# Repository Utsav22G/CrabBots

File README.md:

# CrabBots
### Small robots that use colored light to interact with other robots and the environment to perform complex interactions. 

## Overview
To learn more about our project, visit our [website!](http://poe.olin.edu/2018/crabworks/)

This github serves a storage capsule for our CAD files, PCB designs, and code used in our project. 

## PCB (Robot)
Our PCB is based off the Arduino Uno and includes some additional features:
* An analog mux for an increased number of anlog input pins
* A dual h-bridge motor driver to power our motors
* A 3-axis accelerometer for tap/bump detection
* Support for an RGB strip. We used NeoPixels

Because our PCB follows the same avr architecture as the Arduino Uno (and uses the same Atmega328P-PB), any Arduino code can be
uploaded through the Arduino IDE compiler to program our boards. However, our boards are lacking usb-serial convertera so an external
usb-serial converter is needed ([this is what we used](https://www.sparkfun.com/products/9825)).

You might notice that our assembled PCBs are populated with only a fraction of the parts that are included in our layout. This is 
due to a radical change in our photodiode sensing circuit after shipping the boards to be manufactured. Fortunately, our new circuit
uses less parts so it's still easy to assemble a working board. 

If you are up for an extra challenge, feel free to submit a pull request for a flashy, new board.

## PCB (Beacon)
What is the best accessory for our CrabBot? A fancy flashlight that can be programmed to display any color and controlled with a
tactile toggle button, of course! Our beacons are a useful tool for debugging and controlling our bots.

The schematic for the board stayed mostly the same. An input for **gnd** and **vcc** are needed for the board to function. We also recommend adding a power switch so the Attiny 85 doesn't drain your battery over time.

## Software
Our final bots rely on two code files: chaser, chased. When uploaded to our CrabBots, this code will make them chase each other. The code is written in Arduino and relys on multiple libraries including the Adafruit sensor library. The appropriate packages that need to be downloaded can be found [here](https://learn.adafruit.com/adafruit-lis3dh-triple-axis-accelerometer-breakout/arduino) and [here](https://learn.adafruit.com/adafruit-neopixel-uberguide/basic-connections). 

## Mechanical Design
The final iteration of CAD can be found here. We printed the components on a Prusa with PLA filament. While this design should not
be constrained by the type of plastic or printer used, we can't guarantee success with another setup. 

## Assembly
While we currently don't have a thorough instruction set layed out, we recommend looking at all our pictures. You probably don't need
or want instructions anyways!

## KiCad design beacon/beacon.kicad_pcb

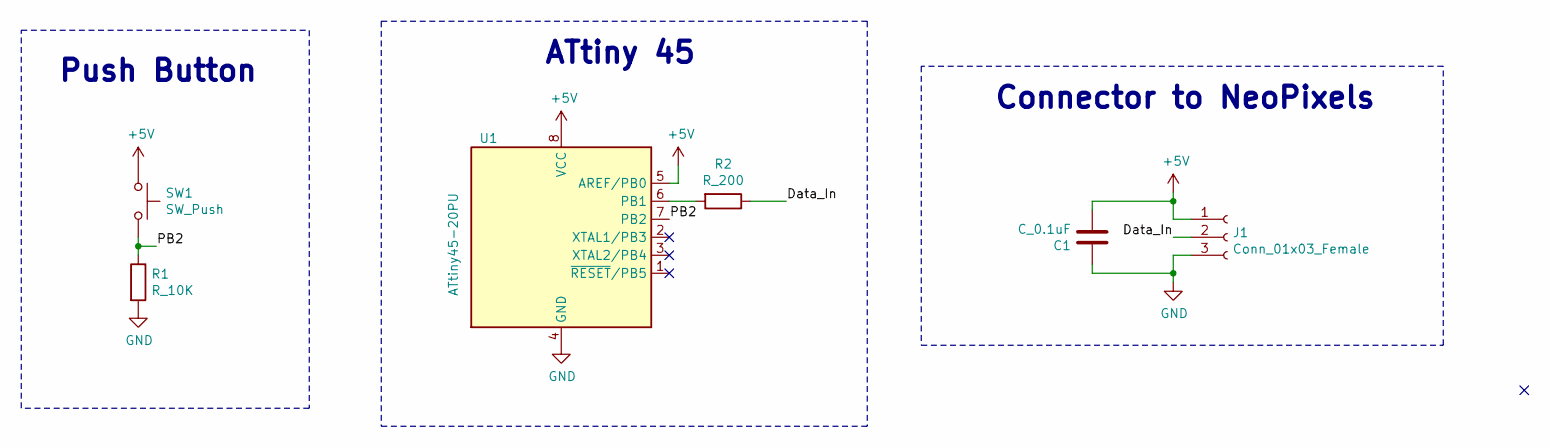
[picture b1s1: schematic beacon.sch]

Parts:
C1: C_0.1uF; C_0805_OEM; MPN 478-3352-1-ND
J1: Conn_01x03_Female; Connector
R1: R_10K; R_0805_OEM; MPN CRS0805-FX-1002ELFCT-ND
R2: R_200; R_0805_OEM; MPN RMCF0805JT200RCT-ND
SW1: SW_Push; push_button
U1: ATtiny45-20PU; DIP-8_W7.62mm_Socket

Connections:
+5V: C1.2, J1.1, SW1.1, U1.5 (AREF/PB0), U1.8 (VCC)
/Data_In: J1.2, R2.1
/PB2: R1.1, SW1.2, U1.7 (PB2)
GND: C1.1, J1.3, R1.2, U1.4 (GND)
unnamed: R2.2, U1.6 (PB1)

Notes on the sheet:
ATtiny 45
Connector to NeoPixels
Push Button

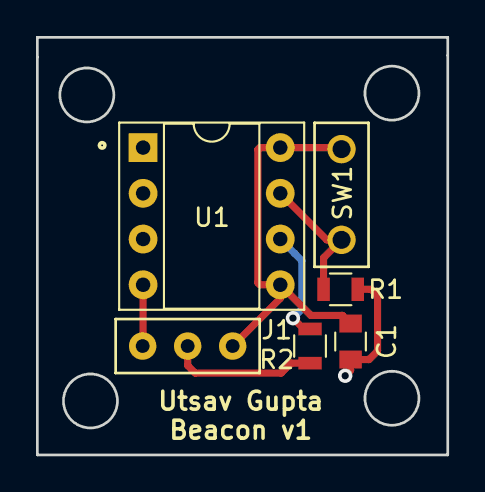
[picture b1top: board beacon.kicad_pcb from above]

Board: 2 copper layers, 22.8 x 23.2 mm, 6 parts (0 on the bottom side), 5 nets.

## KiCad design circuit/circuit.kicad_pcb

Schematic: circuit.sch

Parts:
C1, C7, C8, C9, C10: C_0.1uF; C_0805_OEM; MPN 478-3352-1-ND
C2, C3: C_30pF; C_0805_OEM; MPN 1276-1130-1-ND
C4: C_100pF; C_0805_OEM; MPN 399-1122-1-ND
C5: C_0.01uF; C_0805_OEM; MPN 478-3352-1-ND
C6: C_2.2uF; R_0805_OEM; MPN 311-1451-1-ND
D1, D2: LED_0805; LED_0805_OEM; MPN 475-1410-1-ND
F1: Fuse_1A; R_0805_OEM
J1: Conn_01x20_Female; Pin_Header_Straight_2x10
J2: Conn_02x03_Odd_Even; Pin_Header_Straight_2x03
P1: CONN_02X03; Pin_Header_Straight_2x03; MPN 609-3234-ND
R1, R2, R7, R9, R19, R21, R29, R30: R_10K; R_0805_OEM; MPN CRS0805-FX-1002ELFCT-ND
R3, R12, R13, R14, R15, R24, R25: R_200; R_0805_OEM; MPN RMCF0805JT200RCT-ND
R4, R5, R16, R17: R_1M; R_0805_OEM; MPN RMCF0805JT1M00CT-ND
R6, R8, R10, R11, R18, R20, R22, R23: R_100K; R_0805_OEM; MPN P100KCCT-ND
R26: R_47K; R_0805_OEM; MPN RNCP0805FTD1K00CT-ND
R27: R_10k; R_0805_OEM; MPN CRS0805-FX-1002ELFCT-ND
R28: R_100; R_0805_OEM; MPN RNCP0805FTD100RCT-ND
U1: LMC6484; SOIC-14_3.9x8.7mm_Pitch1.27mm
U2: LIS3DHTR
U3, U4: LM358DT; SO-8_5.3x6.2mm_Pitch1.27mm
U5: L78M05CDT-TR
U6: LM3480; SOT-23; MPN LM3480IM3-3.3CT-ND
U7, U8: SN74LV4052APWR; TSSOP-16_4.4x5mm_Pitch0.65mm
U9: DRV8834; DRV8834PWP
U10: ATmega328P-PU; ATMEGA_328PB_CONN
Y1: Crystal_SMD; Crystal_SMD_FA238; MPN 887-1125-1-ND

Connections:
/3.3V: C8.1, C10.1, R1.2, R2.2, R30.1, U2.1, U2.14, U6.1
/MISO: P1.1, U10.18 (PB4)
/MOSI: P1.4, U10.17 (PB3)
/RESET: P1.5, R27.2, U10.1 (~RESET~/PC6)
/SCK: P1.3, U10.19 (PB5)
/SCL: R2.1, U2.4, U10.28 (PC5)
/SDA: R1.1, U2.6, U10.27 (PC4)
/battery+: C5.2, D1.2, F1.1, U5.1 (GND), U9.18, U9.19
/blue_1: J1.16, U7.1
/blue_2: J1.15, U7.5
/blue_3: J1.14, U7.2
/blue_4: J1.13, U7.4
/blue_5: J1.8, U8.1
/blue_6: J1.7, U8.5
/blue_7: J1.6, U8.2
/blue_8: J1.5, U8.4
/blue_inA: R17.2, U1.9 (-), U7.3
/blue_inB: R16.2, U1.13 (-), U8.3
/blue_outA: R25.1, U10.24 (PC1)
/blue_outB: R24.1, U10.26 (PC3)
/issues: U9.16, U10.12 (PD6)
/led_D1: R3.1, U10.13 (PD7)
/motorA+: J2.1, U9.4
/motorA-: J2.2, U9.6
/motorA_DIR: U9.13, U10.6 (PD4)
/motorA_PWM: U9.10, U10.15 (PB1)
/motorB+: J2.3, U9.9
/motorB-: J2.4, U9.7
/motorB_DIR: U9.12, U10.11 (PD5)
/motorB_PWM: U9.11, U10.16 (PB2)
/p_led: D2.2, U10.14 (PB0)
/red_1: J1.12, U7.12
/red_2: J1.11, U7.14
/red_3: J1.10, U7.15
/red_4: J1.9, U7.11
/red_5: J1.4, U8.12
/red_6: J1.3, U8.14
/red_7: J1.2, U8.15
/red_8: J1.1, U8.11
/red_inA: R4.2, U1.2 (-), U7.13
/red_inB: R5.2, U1.6 (-), U8.13
/red_outA: R12.1, U10.23 (PC0)
/red_outB: R13.1, U10.25 (PC2)
/select_0A: U7.10, U10.2 (PD0)
/select_0B: U8.10, U10.4 (PD2)
/select_1A: U7.9, U10.3 (PD1)
/select_1B: U8.9, U10.5 (PD3)
unnamed: C2.1, U10.9 (XTAL1/PB6), Y1.3
unnamed: C3.1, U10.10 (XTAL2/PB7), Y1.1
unnamed: C4.2, R28.1, U10.20 (AVCC)
unnamed: C5.1, U9.17
unnamed: D1.1, R14.2
unnamed: D2.1, R15.2
unnamed: F1.2, J2.5
unnamed: J1.19, R3.2
unnamed: R4.1, R7.2, U1.1
unnamed: R5.1, R9.2, U1.7
unnamed: R7.1, U3.3
unnamed: R9.1, U4.3
unnamed: R10.1, R12.2, U3.1
unnamed: R6.2, R10.2, U3.2
unnamed: R11.1, R13.2, U4.1
unnamed: R8.2, R11.2, U4.2
unnamed: R16.1, R19.2, U1.14
unnamed: R17.1, R21.2, U1.8
unnamed: R18.2, R22.2, U4.6
unnamed: R19.1, U4.5
unnamed: R20.2, R23.2, U3.6
unnamed: R21.1, U3.5
unnamed: R22.1, R24.2, U4.7
unnamed: R23.1, R25.2, U3.7
unnamed: R26.2, U9.1
unnamed: R29.1, U2.7
unnamed: R30.2, U2.8
VCC: C1.2, C6.1, C7.1, C9.1, J1.17, J1.18, P1.2, R26.1, R27.1, R28.2, U1.4 (V+), U3.8, U4.8, U5.2 (VO), U6.2, U7.16, U8.16, U9.20, U9.22, U9.23, U9.24, U10.7 (VCC)

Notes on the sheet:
RED DIODE CIRCUIT
BLUE DIODE CIRCUIT
ORIGINAL CIRCUIT
NEW CIRCUIT
CONNECTORS
MOTOR DRIVER
POWER REGULATORS
MAIN
PROGRAMMING
POWER
AUXILIARY HARDWARE
PINOUT
SUPPORTING IMAGES
LEDS
ACCELEROMETER

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
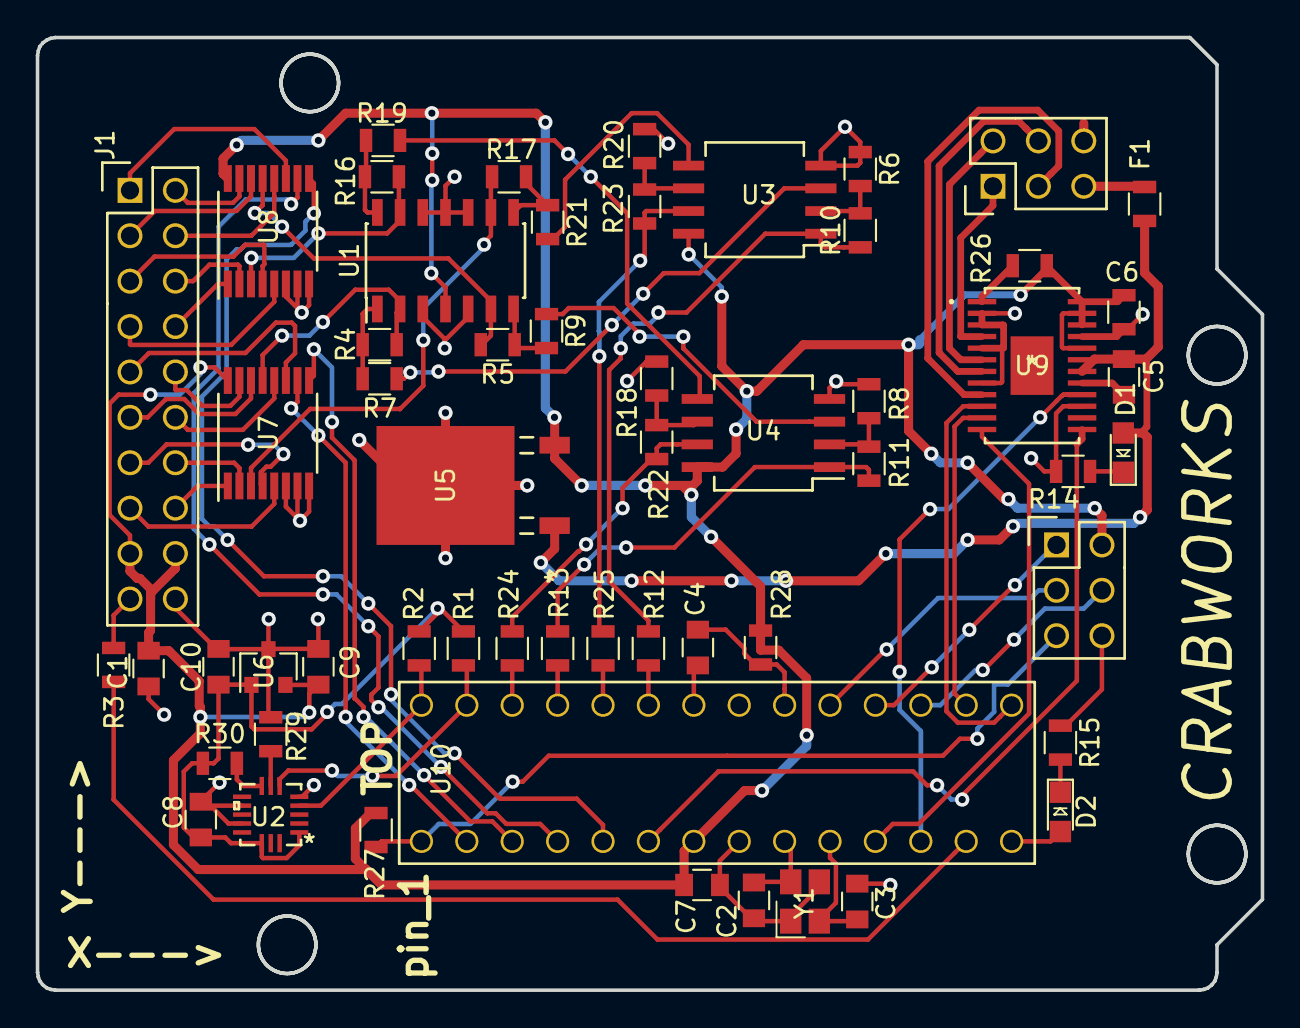
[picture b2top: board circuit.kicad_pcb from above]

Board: 2 copper layers, 68.5 x 53.3 mm, 57 parts (0 on the bottom side), 76 nets.

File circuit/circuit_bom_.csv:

Component,Description,Part,References,Value,Footprint,Quantity Per PCB,Datasheet,MPN,MFN,PurchasingLink,Package,Purchasing Link
1,"Capacitor, 0.1uF, 50V, 5%, 0805",C_0.1uF,C5,C_0.01uF,C_0805_OEM,1,http://datasheets.avx.com/X7RDielectric.pdf,478-3352-1-ND,DK,https://www.digikey.com/product-detail/en/samsung-electro-me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,,
2,"Capacitor, 0.1uF, 50V, 5%, 0805",C_0.1uF,C1 C7 C8 C9 C10,C_0.1uF,C_0805_OEM,5,http://datasheets.avx.com/X7RDielectric.pdf,478-3352-1-ND,DK Digi-Key,https://www.digikey.com/products/en?keywords=478-3352-1-ND,Value,
3,"Capacitor, 100pF, 50V, 5%, 0805",C_100pF,C4,C_100pF,C_0805_OEM,1,https://content.kemet.com/datasheets/KEM_C1003_C0G_SMD.pdf,399-1122-1-ND,Digi-Key,https://www.digikey.com/product-detail/en/kemet/C0805C101J5G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,Value,
4,"Capacitor, 2.2uF, 10V, 10%, 0603",C_2.2uF,C6,C_2.2uF,R_0805_OEM,1,http://www.yageo.com/documents/recent/UPY-GPHC_X5R_4V-to-50V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,311-1451-1-ND,DK,https://www.digikey.com/product-detail/en/taiyo-yuden/EMK212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,,
5,"Capacitor, 30pF, 50V, 5%, 0805",C_30pF,C2 C3,C_30pF,C_0805_OEM,2,https://media.digikey.com/pdf/Data%20Sheets/Samsung%20PDFs/C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,1276-1130-1-ND,DK,https://www.digikey.com/product-detail/en/samsung-electro-me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,,
6,"LED, Green, 2.2V, 20mA, 0805",LED_0805,D1 D2,LED_0805,LED_0805_OEM,2,http://www.osram-os.com/Graphics/XPic9/00078860_0.pdf,475-1410-1-ND,DK,https://www.digikey.com/products/en?keywords=475-1410-1-ND,,
7,Fuse,Fuse,F1,Fuse_1A,R_0805_OEM,1,https://industrial.panasonic.com/cdbs/www-data/pdf/AFA0000/A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,,,,,
8,"Generic connector, single row, 01x20, script generated (kicad-library-utils/schlib/autogen/connector/)",Conn_01x20_Female,J1,Conn_01x20_Female,Pin_Header_Straight_2x10,1,~,,,,,
9,"Generic connector, double row, 02x03, odd/even pin numbering scheme (row 1 odd numbers, row 2 even numbers), script generated (kicad-library-utils/schlib/autogen/connector/)",Conn_02x03_Odd_Even,J2,Conn_02x03_Odd_Even,Pin_Header_Straight_2x03,1,~,,,,,
10,,CONN_02X03-formula,P1,CONN_02X03,Pin_Header_Straight_2x03,1,http://portal.fciconnect.com/Comergent//fci/drawing/67996.pdf,609-3234-ND,Digi-Key,https://www.digikey.com/product-detail/en/amphenol-fci/67997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,Value,
11,,R_100,R28,R_100,R_0805_OEM,1,https://www.seielect.com/Catalog/SEI-rncp.pdf,RNCP0805FTD100RCT-ND,Digi-Key,https://www.digikey.com/products/en?keywords=RNCP0805FTD100RCT-ND,Value,
12,,R_100K,R6 R8 R10 R11 R18 R20 R22 R23,R_100K,R_0805_OEM,8,https://industrial.panasonic.com/cdbs/www-data/pdf/RDA0000/A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,P100KCCT-ND,DK,https://www.digikey.com/product-detail/en/panasonic-electron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,,
13,,R_10K,R1 R2 R7 R9 R19 R21 R29 R30,R_10K,R_0805_OEM,8,http://www.bourns.com/data/global/pdfs/CRS.pdf,CRS0805-FX-1002ELFCT-ND,DK,https://www.digikey.com/products/en?keywords=CRS0805-FX-1002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,,
14,,R_10k-formula,R27,R_10k,R_0805_OEM,1,http://www.bourns.com/data/global/pdfs/CRS.pdf,CRS0805-FX-1002ELFCT-ND,Digi-Key,https://www.digikey.com/products/en?keywords=CRS0805-FX-1002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,Value,
15,,R_1M,R4 R5 R16 R17,R_1M,R_0805_OEM,4,https://www.seielect.com/Catalog/SEI-rncp.pdf,RMCF0805JT1M00CT-ND,DK,https://www.digikey.com/product-detail/en/stackpole-electron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,,
16,,R_200,R3 R12 R13 R14 R15 R24 R25,R_200,R_0805_OEM,7,https://www.seielect.com/Catalog/SEI-RMCF_RMCP.pdf,RMCF0805JT200RCT-ND,DK,https://www.digikey.com/products/en?keywords=RMCF0805JT200RCT-ND,,
17,,R_1K,R26,R_47K,R_0805_OEM,1,https://www.seielect.com/Catalog/SEI-rncp.pdf,RNCP0805FTD1K00CT-ND,DK,https://www.digikey.com/products/en?keywords=RNCP0805FTD1K00CT-ND,,
18,,ATmega328P-PU-MCU_Microchip_ATmega,U10,ATmega328P-PU,ATMEGA_328PB_CONN,1,http://ww1.microchip.com/downloads/en/DeviceDoc/ATmega328_P%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,,,,,
19,,DRV8834-formula,U9,DRV8834,DRV8834PWP,1,www.ti.com/lit/ds/symlink/drv8834.pdf,,,,,https://www.digikey.com/product-detail/en/texas-instruments/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
20,"1A Low Dropout regulator, positive, 5.0V fixed output, SOT-223",AMS1117-5.0,U5,L78M05CDT-TR ,L78M05CDT-TR,1,www.st.com/content/ccc/resource/technical/document/datasheet/d7/5f/dc/5c/d5/b6/48/7c/CD00000447.pdf/files/CD00000447.pdf/jcr:content/translations/en.CD00000447.pdf,,,,,
21,,LIS3DHTR-formula,U2,LIS3DHTR,LIS3DHTR,1,,,,,,
22,"Linear regulator, 30V max input, 3.3V output, 100mA",LM3480,U6,LM3480,SOT-23,1,http://www.ti.com/lit/ds/symlink/lm3480.pdf,LM3480IM3-3.3CT-ND,DK,https://www.digikey.com/product-detail/en/texas-instruments/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,,
23,,LM358DT-formula,U3 U4,LM358DT,SO-8_5.3x6.2mm_Pitch1.27mm,2,www.st.com/content/ccc/resource/technical/document/datasheet/61/46/87/01/98/ed/44/c5/CD00000464.pdf/files/CD00000464.pdf/jcr:content/translations/en.CD00000464.pdf,,,https://www.digikey.com/product-detail/en/stmicroelectronics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,,
24,"Quad CMOS Rail-to-Rail Input and Output Operational Amplifier, DIP-14/SOIC-14",LMC6484,U1,LMC6484,SOIC-14_3.9x8.7mm_Pitch1.27mm,1,http://www.ti.com/lit/ds/symlink/lmc6484.pdf,,,,,
25,,SN74LV4052APWR-formula,U7 U8,SN74LV4052APWR,TSSOP-16_4.4x5mm_Pitch0.65mm,2,www.ti.com/lit/ds/symlink/sn74lv4052a.pdf,,,,,https://www.digikey.com/product-detail/en/texas-instruments/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
26,CRYSTAL 16.0000MHZ 18PF SMD,Crystal_SMD,Y1,Crystal_SMD,Crystal_SMD_FA238,1,http://www.txccorp.com/download/products/quartz_crystals/201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,887-1125-1-ND,DK,https://www.digikey.com/product-detail/en/txc-corporation/7M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,,
,,,,,,,,,,,,
,,,,,,,,,,,,
,,,,,,,,,,,,
,,,,,,,,,,,,
,,,,,,,,,,,,
Component Groups:,26,,,,,,,,,,,
Component Count:,57,,,,,,,,,,,
Fitted Components:,57,,,,,,,,,,,
Number of PCBs:,1,,,,,,,,,,,
Total components:,57,,,,,,,,,,,
Schematic Version:,,,,,,,,,,,,
Schematic Date:,,,,,,,,,,,,
BoM Date:,Wed 21 Nov 2018 11:47:25 PM EST,,,,,,,,,,,
Schematic Source:,/home/utsav22g/Olin Stuff/CrabBots/circuit/circuit.sch,,,,,,,,,,,
KiCad Version:,Eeschema 5.0.1-33cea8e~68~ubuntu18.04.1,,,,,,,,,,,

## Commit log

2018-10-17 Luminosity detector
2018-10-21 added new code for reading sensor values that could have changing frequencies
2018-10-21 added a schematic for our circuit
2018-10-28 added color sense code
2018-10-31 NeoPixels working code
2018-10-31 made progress on schematic
2018-11-01 Controlling NeoPixels with ATtiny45
2018-11-04 more progess git add -A!
2018-11-04 finished schematic for main board
2018-11-05 started on layout. *make crab noise*
2018-11-06 finished board
2018-11-06 Adding beacon schematic
2018-11-06 generated gerber files
2018-11-06 Adding gerber files
2018-11-07 added pictures of the pcb
2018-11-13 added accel pics
2018-11-25 added pics of layout for pcb
2018-11-25 added arduino code
2018-11-27 added more pics
2018-11-29 added code for driving
2018-11-29 added more driving commands to crashing.ino
2018-11-30 new pic
2018-11-30 diodetest is to set mux and test photodiodes/motors
2018-12-02 full code added into vectorizedmotion
2018-12-12 updated arduino code. vectorizedmotion is most recent motion code
2018-12-12 added a few test scr ipts
2018-12-13 chasing and chased code
2018-12-13 code updates
2018-12-13 kinda works
2018-12-13 CAD files
2018-12-14 Added a LED circuit
2018-12-14 Added a new LED circuit
2018-12-14 added a pdf of our schematic
2018-12-14 Added a Readme
    consider crabs
2018-12-14 Fixed Links
    The long week is starting to show itself.
2018-12-17 code for new bots
2018-12-24 added a picture

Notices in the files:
parts and their libraries:
Copyright 2016 Accelerated Designs. All rights reserved.
